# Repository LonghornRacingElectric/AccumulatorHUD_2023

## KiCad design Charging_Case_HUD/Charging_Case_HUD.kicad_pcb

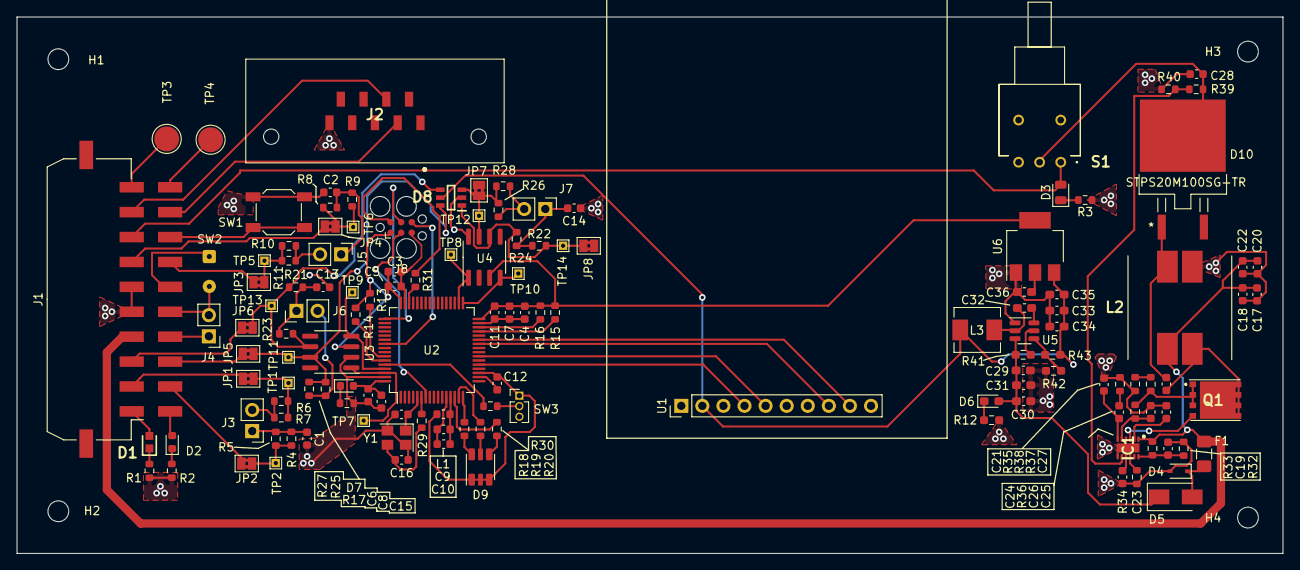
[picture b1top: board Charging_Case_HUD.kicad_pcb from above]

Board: 2 copper layers, 152.5 x 64.6 mm, 140 parts (0 on the bottom side), 91 nets.

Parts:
C1, C2, C13, C14: 4.7n; C_0603_1608Metric
C3: 4u7; C_0603_1608Metric
C4, C5, C6, C7, C8, C22: 100n; C_0603_1608Metric
C9, C25: 1u; C_0603_1608Metric
C10: 10n; C_0603_1608Metric
C11, C12: 0u1; C_0603_1608Metric
C15, C16: 10p; C_0603_1608Metric
C17, C18, C20: 10u; C_0603_1608Metric
C19, C26: 100p; C_0603_1608Metric
C21: 270p; C_0603_1608Metric
C23: 220n; C_0603_1608Metric
C24: 6.8n; C_0603_1608Metric
C27: 9.4u; C_0603_1608Metric
C28: 66u; C_0603_1608Metric
C29, C30: 10uF; C_0603_1608Metric_Pad1.08x0.95mm_HandSolder
C31, C32: 100nF; C_0603_1608Metric_Pad1.08x0.95mm_HandSolder
C33, C34, C36: 22uF; C_0603_1608Metric_Pad1.08x0.95mm_HandSolder
C35: 1uF; C_0603_1608Metric_Pad1.08x0.95mm_HandSolder
D1: IMD; LEDC1608X80N
D2: AMS; LED_0603_1608Metric
D3: VCU Wake; LED_0805_2012Metric
D4: 32V; D_SOD-323
D5: 0.7dV; D_SMA
D6: LED; LED_0603_1608Metric_Pad1.05x0.95mm_HandSolder
D7: RED; LED_0603_1608Metric
D8: DT1446-04TS-7; SOT95P280X100-6N
D9: SMLVN6RGB; LED_ROHM_SMLVN6
D10: STPS20M100SG-TR
F1: 2A; Fuse_1206_3216Metric_Pad1.42x1.75mm_HandSolder
H1, H2, H3, H4: MountingHole; MountingHole_2.5mm
IC1: LM5155DSSR; SON50P200X300X80-13N-D
J1: Conn_01x20; Molex_Micro-Fit_3.0_43045-2010_2x10-1MP_P3.00mm_Horizontal
J2: 09551296822741
J3, J4, J5, J6, J7: Conn_01x02; PinHeader_1x02_P2.54mm_Vertical
J8: SWD; Tag-Connect_TC2030-IDC-FP_2x03_P1.27mm_Vertical
JP1, JP2, JP3, JP4, JP5, JP6, JP7, JP8: SolderJumper-2_P1.3mm_Bridged2Bar_Pad1.0x1.5mm
L1: 68n; L_0603_1608Metric
L2: 7448700015; WE-DD_12XX_CROSSED12
L3: 4u7; L_Sunlord_MWSA0518_5.4x5.2mm
Q1: CSD18537NQ5A; CSD19531Q5AT
R1, R2: 150; R_0603_1608Metric
R3: 500; R_0603_1608Metric
R4, R5, R6, R7, R8, R9, R10, R11, R21, R22, R23, R24, R25, R26, R27, R28: 120; R_0603_1608Metric
R12: 470R; R_0603_1608Metric_Pad0.98x0.95mm_HandSolder
R13, R14, R15, R16: 2k2; R_0603_1608Metric
R17, R36: 100; R_0603_1608Metric
R18, R19, R20: 220; R_0603_1608Metric
R29: 47; R_0603_1608Metric
R30: 10K; R_0603_1608Metric
R31: 22; R_0603_1608Metric
R32: 6k8; R_0603_1608Metric
R33: 34k8; R_0603_1608Metric
R34: 17k8; R_0603_1608Metric
R35: 10k; R_0603_1608Metric
R37, R38: 4m; R_0603_1608Metric
R39: 51k1; R_0603_1608Metric
R40: 4k7; R_0603_1608Metric
R41, R42: 10K; R_0603_1608Metric_Pad0.98x0.95mm_HandSolder
R43: 54.9K; R_0603_1608Metric_Pad0.98x0.95mm_HandSolder
S1: 465031772505
SW1: SW_MEC_5G; SW_SPST_SKQG_WithStem
SW2: SW_DIP_x01; SolderWire-0.1sqmm_1x02_P3.6mm_D0.4mm_OD1mm
SW3: SW_SPDT; PinHeader_1x03_P1.27mm_Vertical
TP1, TP2, TP5, TP6, TP7, TP8, TP9, TP10, TP11, TP12, TP13, TP14: TestPoint_THTPad_1.0x1.0mm_Drill0.5mm
TP3: Pilot; TestPoint_Pad_D3.0mm
TP4: Prox; TestPoint_Pad_D3.0mm
U1: ILI9163C; PinHeader_1x10_P2.54mm_Vertical
U2: STM32F105RCTx; LQFP-64_10x10mm_P0.5mm
U3, U4: SN65HVD230; SOIC-8_3.9x4.9mm_P1.27mm
U5: LMR51420; SOT-23-6
U6: AMS1117-3.3; SOT-223-3_TabPin2
Y1: 16MHz; Crystal_SMD_3225-4Pin_3.2x2.5mm

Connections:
+3.3VA: C9.1, C10.1, L1.2, U2.13 (VDDA)
+3V3: C3.1, C4.1, C5.1, C6.1, C7.1, C8.1, C11.1, C12.1, C36.1, D7.2 (A), D9.1 (BA), D9.2 (RA), D9.3 (GA), J8.1, L1.1, R13.1, R14.1, R15.1, R16.1, SW3.1 (A), U2.1 (VBAT), U2.19 (VDD), U2.32 (VDD), U2.48 (VDD), U2.64 (VDD), U3.3 (VCC), U4.3 (VCC), U6.2 (VO)
+5V: C33.1, C34.1, C35.1, D8.5 (VCC), L3.2, R43.2, U1.2 (VIN), U6.3 (VI)
+12V: C28.1, D10.3, R39.1, S1.2 (COM)
+24V: C17.1, C18.1, C20.1, C22.1, F1.2, IC1.1 (BIAS), J1.4, L2.1, R33.1
/MCU2/BOOT0: R30.2, U2.60 (BOOT0)
/MCU2/CAN1_RX: TP9.1, U2.61 (PB8), U3.4 (R)
/MCU2/CAN1_TX: TP7.1, U2.62 (PB9), U3.1 (D)
/MCU2/CAN2_RX: TP10.1, U2.33 (PB12), U4.4 (R)
/MCU2/CAN2_TX: TP8.1, U2.34 (PB13), U4.1 (D)
/MCU2/HSE_in: C15.1, U2.5 (PD0), Y1.1
/MCU2/HSE_out: R29.1, U2.6 (PD1)
/MCU2/I2C1_SCL: R13.2, U2.58 (PB6)
/MCU2/I2C1_SDA: R14.2, U2.59 (PB7)
/MCU2/I2C2_SCL: R15.2, U2.29 (PB10)
/MCU2/I2C2_SDA: R16.2, U2.30 (PB11)
/MCU2/LED_B: R18.2, U2.16 (PA2)
/MCU2/LED_G: R19.2, U2.15 (PA1)
/MCU2/LED_R: R20.2, U2.14 (PA0)
/MCU2/NRST: J8.3, U2.7 (NRST)
/MCU2/PB3: J8.6, U2.55 (PB3)
/MCU2/SWCLK: J8.4, U2.49 (PA14)
/MCU2/SWDIO: R31.2, U2.46 (PA13)
/SEPIC_CAD/COMP: C21.1, C24.1, IC1.6 (COMP)
/SEPIC_CAD/FB: IC1.8 (FB), R39.2, R40.1
/SEPIC_CAD/RT: IC1.10 (RT), R34.2
/SEPIC_CAD/SS: C23.1, IC1.9 (SS)
/SEPIC_CAD/UVLO: C19.1, IC1.12 (UVLO/SYNC), R32.1, R33.2
/StandardizedVRMS/BUCK/EN: R41.2, U5.5 (EN)
/StandardizedVRMS/BUCK/SW: C32.1, L3.1, U5.2 (SW)
/StandardizedVRMS/BUCK/VBST: C32.2, U5.6 (VBST)
/StandardizedVRMS/BUCK/VFB: R42.1, R43.1, U5.4 (VFB)
/StandardizedVRMS/BUCK/V_in: C29.1, C30.1, C31.1, D5.1 (K), D6.2 (A), R41.1, U5.3 (VIN)
/StandardizedVRMS/DIODE: D4.1 (K), D5.2 (A), F1.1
AMS_LED: D2.2 (A), J1.11
CAN1_H: J1.9, J2.7
CAN1_L: J1.19, J2.2
CAN2_H: J1.2, JP1.2 (B)
CAN2_L: J1.12, JP2.2 (B)
CAN3_H: J1.17, JP3.2 (B)
CAN3_L: J1.7, JP4.2 (B)
CAN4_H: J1.13, JP5.2 (B)
CAN4_L: J1.3, JP6.2 (B)
CAN_Shield: C1.1, C2.1, C3.2, C4.2, C5.2, C6.2, C7.2, C8.2, C9.2, C10.2, C11.2, C12.2, C13.1, C14.1, C15.2, C16.2, C17.2, C18.2, C19.2, C20.2, C21.2, C22.2, C23.2, C25.1, C26.1, C28.2, C29.2, C30.2, C31.2, C33.2, C34.2, C35.2, C36.2, D4.2 (A), D8.2 (VSS), IC1.4 (PGND), IC1.7 (AGND), IC1.13 (EP), J1.5, J1.6, J2.5, J8.5, L2.3, R1.1, R2.1, R3.1, R12.1, R17.2, R32.2, R34.1, R35.2, R38.2, R40.2, R42.2, SW1.2 (B), SW3.3 (C), U1.1 (GND), U2.12 (VSSA), U2.18 (VSS), U2.31 (VSS), U2.47 (VSS), U2.63 (VSS), U3.2 (GND), U3.8 (Rs), U4.2 (GND), U4.8 (Rs), U5.1 (GND), U6.1 (GND), Y1.2, Y1.4
CS: U1.9 (LCDCS), U2.27 (PB1)
D/C: U1.8 (D/C), U2.26 (PB0)
IMD_LED: D1.2 (A), J1.1
J1772_Pilot: J1.10, TP3.1
J1772_Prox: J1.20, TP4.1
MOSI: U1.5 (MOSI), U2.23 (PA7)
unnamed: C1.2, J3.1, R4.1, R5.1
unnamed: C2.2, J5.1, R8.1, R9.1
unnamed: C13.2, J6.1, R21.1, R23.1
unnamed: C14.2, J7.1, R22.1, R24.1
unnamed: C16.1, R29.2, Y1.3
unnamed: C24.2, R35.1
unnamed: C25.2, IC1.2 (VCC)
unnamed: C26.2, IC1.5 (CS), R36.2
unnamed: C27.1, D10.1, L2.4
unnamed: C27.2, L2.2, Q1.5 (D_1), Q1.6 (D_2), Q1.7 (D_3), Q1.8 (D_4)
unnamed: D1.1 (K), R1.2
unnamed: D2.1 (K), R2.2
unnamed: D3.1 (K), R3.2
unnamed: D6.1 (K), R12.2
unnamed: D7.1 (K), R17.1
unnamed: D8.1 (I/O1), JP8.1 (A), R22.2, R24.2, TP14.1, U4.6 (CANL)
unnamed: D8.3 (I/O2), JP7.1 (A), R26.1, R28.1, TP12.1, U4.7 (CANH)
unnamed: D8.4 (I/O3), JP6.1 (A), R21.2, R23.2, TP13.1, U3.6 (CANL)
unnamed: D8.6 (I/O4), JP5.1 (A), R25.1, R27.1, TP11.1, U3.7 (CANH)
unnamed: D9.4 (GK), R20.1
unnamed: D9.5 (RK), R19.1
unnamed: D9.6 (BK), R18.1
unnamed: IC1.3 (GATE), Q1.4 (G)
unnamed: J3.2, R6.2, R7.2
unnamed: J5.2, R10.2, R11.2
unnamed: J6.2, R25.2, R27.2
unnamed: J7.2, R26.2, R28.2
unnamed: J8.2, R31.1
unnamed: JP1.1 (A), R6.1, R7.1, TP1.1
unnamed: JP2.1 (A), R4.2, R5.2, TP2.1
unnamed: JP3.1 (A), R10.1, R11.1, TP5.1
unnamed: JP4.1 (A), R8.2, R9.2, TP6.1
unnamed: Q1.1 (S_1), Q1.2 (S_2), Q1.3 (S_3), R36.1, R37.1
unnamed: R30.1, SW3.2 (B)
unnamed: R37.2, R38.1
SCK: U1.4 (SCLK), U2.21 (PA5)
Shutdown_CON: J1.15, J4.2, SW2.2
Shutdown_IN: J1.14, J4.1
Shutdown_OUT: J1.16, SW2.1
TSCU_Rst: J1.18, SW1.1 (A)
VCU_Wake: D3.2 (A), J1.8, S1.1 (NO)

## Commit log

2022-09-26 Added 2023KicadLibrary
2022-11-27 second review
2022-12-04 try 1
2022-12-11 with layout
2022-12-12 PCB stuff
2022-12-21 new HUD PCB
2022-12-21 revisions
2022-12-23 updated connector

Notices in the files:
parts and their libraries:
Copyright 2021 Accelerated Designs. All rights reserved.
